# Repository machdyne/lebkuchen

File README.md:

# Lebkuchen Computer

Lebkuchen is an FPGA computer based on the GateMate A1.

This repo contains schematics, PCB layouts, pinouts, a 3D-printable case, example gateware and documentation.

Find more information on the [Lebkuchen product page](https://machdyne.com/product/lebkuchen-computer/).

## Programming Lebkuchen 

Lebkuchen can be programmed over USB-C or by copying gateware to a MicroSD card (not yet implemented). The FPGA is configured by the onboard RP2040, which can load the configuration from onboard flash, a FAT-formatted MicroSD card or over the USB-JTAG bridge.

### JTAG

Program the FPGA configuration SRAM:

```
openFPGALoader -c dirtyJtag image.bit
```

### 3.5mm TRRS Audio Jack

| Pin | Signal |
| --- | ------ |
| T | Left Audio |
| R1 | Right Audio |
| R2 | Composite Video |
| S | GND |

## Resources

 * [fpga-dac audio player](https://github.com/machdyne/fpga-dac)

## License

The contents of this repo are released under the [Lone Dynamics Open License](LICENSE.md).

Note: You can use these designs for commercial purposes but we ask that instead of producing exact clones, that you either replace our trademarks and logos with your own or add your own next to ours.

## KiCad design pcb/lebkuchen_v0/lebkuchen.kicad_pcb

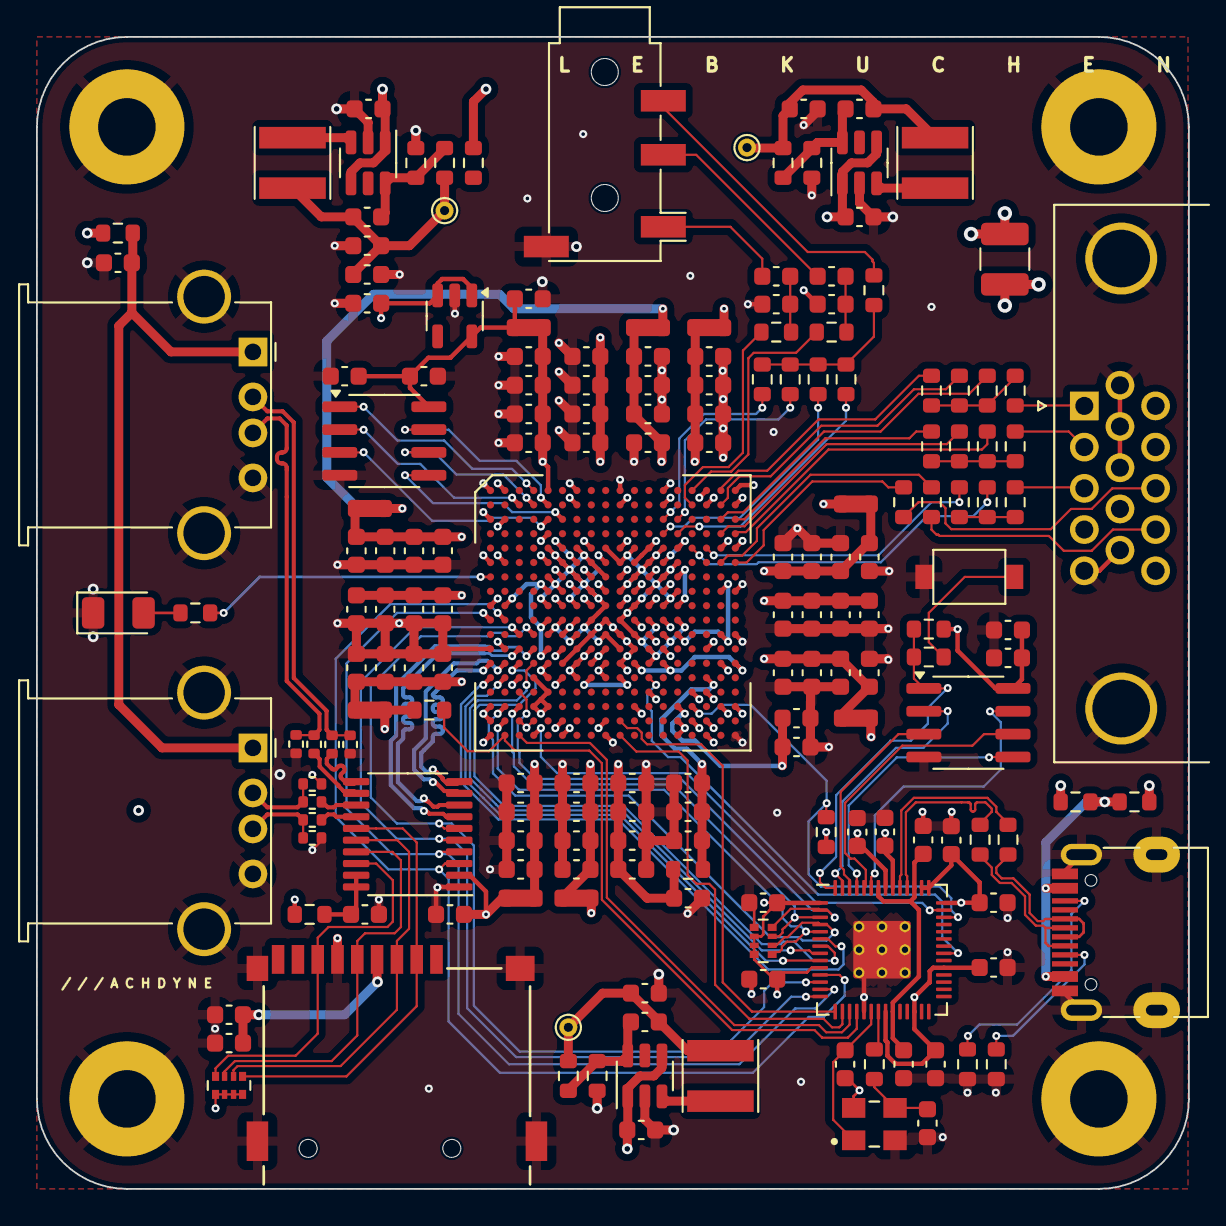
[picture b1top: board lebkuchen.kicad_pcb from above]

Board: 4 copper layers, 64.0 x 64.0 mm, 185 parts (0 on the bottom side), 116 nets.

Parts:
C1, C2, C3, C12, C16, C18, C19, C27, C28, C36, C37, C45, C46, C55, C56: 2.2uF; C_0603_1608Metric
C4, C5, C6, C21, C22, C29, C30, C38, C39, C47, C48, C57, C58: 470nF; C_0603_1608Metric
C7: 220nF; C_0603_1608Metric
C8, C9, C10, C11, C17, C20, C23, C24, C31, C32, C40, C41, C49, C50, C59, C60, C64, C65, C67, C68, C69, C71, C83, C84, C85, C86, C87, C88, C90, C91, C95: 100nF; C_0603_1608Metric
C13, C14, C15, C25, C26, C33, C34, C42, C43, C51, C52, C61, C62: 10nF; C_0603_1608Metric
C35, C66, C89, C96, C97: 1uF; C_0603_1608Metric
C44, C80, C81: 22uF; C_0603_1608Metric
C53, C78, C79, C92, C93, C94: 10uF; C_0603_1608Metric
C54, C63: 15pF; C_0603_1608Metric
C72, C73, C74: 4.7uF; C_0603_1608Metric
C75, C76, C77: 10pF; C_0603_1608Metric
D2: LED; LED_1206_3216Metric
F1: Polyfuse; Fuse_1210_3225Metric
FB1, FB2, FB3, FB4: Ferrite_Bead; R_0603_1608Metric
H1, H2, H3, H4: MountingHole_Pad; MountingHole_3.2mm_M3_Pad
J1: TYPE-C-31-M-12-FIXED; USB_C_Receptacle_HRO_TYPE-C-31-M-12-BIG-PADS-PASTE
J3: AudioJack4; Jack_3.5mm_PJ320D_Horizontal
J4: MICROSD; SDCARD
J5, J6: USB_A; USB_A_Stewart_SS-52100-001_Horizontal
L1, L2, L3: 2.2uH; L_Taiyo-Yuden_MD-4040
R1: 4K7; R_0603_1608Metric
R2, R20: 5K1; R_0603_1608Metric
R6, R38: 10K; R_0603_1608Metric
R9, R11, R12, R13, R14, R16, R17, R18, R19: 0R; LD-NETTIE-0603
R10, R15: 27R; R_0603_1608Metric
R23, R24: 200K; R_0603_1608Metric
R25: 44K2; R_0603_1608Metric
R26, R29: 150K; R_0603_1608Metric
R27: 47K; R_0603_1608Metric
R28: 100K; R_0603_1608Metric
R30: 22R; R_0603_1608Metric
R31, R32, R33, R34: 22R; R_0402_1005Metric
R37, R39, R44, R51, R54, R58: 1K; R_0603_1608Metric
R40, R41, R67, R68: 100R; R_0603_1608Metric
R42, R52, R56, R60: 270R; R_0603_1608Metric
R43, R53, R57, R61: 536R; R_0603_1608Metric
R45: 2K; R_0603_1608Metric
R47, R64, R65, R66: 51R; R_0603_1608Metric
R55, R59, R62, R63: 15K; R_0402_1005Metric
RN1: 20K; R_Array_Convex_4x0402
RN2: 4K7; R_Array_Convex_4x0402
SW1: BOOT; Button_2P_3x4mm
TP1: TP_PWR3V3; TestPoint_THTPad_D1.0mm_Drill0.5mm
TP2: TP_PWR2V5; TestPoint_THTPad_D1.0mm_Drill0.5mm
TP3: TP_PWR1V0; TestPoint_THTPad_D1.0mm_Drill0.5mm
U1: CCGM1A1; BGA-324_15.0x15.0mm_Layout18x18_P0.8mm_Ball0.5mm_Pad0.4mm_N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
U2: RP2040; RP2040-QFN-56-OFFICIAL
U3: APS6404L-SQN-SN; SOIC-8_3.9x4.9mm_P1.27mm
U4: LSF0108PWR; TSSOP-20_4.4x6.5mm_P0.65mm
U5: AT25FF321A-SSHN-B; SOIC-8_3.9x4.9mm_P1.27mm
U7: NCP164ASN180T1G; TSOT-23-5
U8, U9, U10: TLV62569DDC; SOT-23-6
VGA1: DB15_Female_MountingHoles; DSUB-15-HD_Female_Horizontal_P2.29x1.98mm_EdgePinOffset3.03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
Y2: ECS-80-12-33-JGN-TR-12MHZ; XTAL_ECS-240-8-33-AGN-TR

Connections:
/AUDIO_L: R40.1, U1.B15 (IO_EB_A8)
/AUDIO_LC: C92.1, J3.T
/AUDIO_R: R41.1, U1.A15 (IO_EB_B8)
/AUDIO_RC: C93.1, J3.R1
/BOOT: R39.1, SW1.1
/CDONE: U1.V3 (IO_WA_B2/CFG_DONE), U2.17 (GPIO14)
/CFAILED: R1.2, U1.V2 (IO_WA_A2/~CFG_FAILED), U2.18 (GPIO15)
/CFG_MD3: U1.V4 (CFG_MD3/IO_WA_B1), U2.41 (GPIO29/ADC3)
/CLKRP: U1.P12 (CLK1/IO_SB_A7), U2.35 (GPIO23)
/CSPI_MISO: U1.P1 (IO_WA_A7/SPI_D1), U2.6 (GPIO4)
/CSPI_MOSI: U1.P2 (IO_WA_B7/SPI_D0), U2.9 (GPIO7)
/CSPI_SCK: U1.N4 (IO_WA_B8/SPI_CLK), U2.8 (GPIO6)
/CSPI_SS: U1.N3 (IO_WA_A8/~SPI_CS), U2.7 (GPIO5)
/JTAG_TCK: RN2.4 (R4.1), U1.R3 (JTAG_TCK/IO_WA_A5), U2.2 (GPIO0)
/JTAG_TDI: RN2.2 (R2.1), U1.T2 (JTAG_TDI/IO_WA_A4), U2.4 (GPIO2)
/JTAG_TDO: RN2.1 (R1.1), U1.U2 (JTAG_TDO/IO_WA_B3), U2.5 (GPIO3)
/JTAG_TMS: RN2.3 (R3.1), U1.T3 (JTAG_TMS/IO_WA_B4), U2.3 (GPIO1)
/LED: R51.1, U1.G1 (IO_WC_A0)
/PWR1V0: C1.2, C2.2, C4.2, C5.2, C9.2, C10.2, C13.2, C14.2, C18.2, C19.2, C20.2, C21.2, C22.2, C23.2, C24.2, C25.2, C26.2, C77.1, C80.1, C81.1, L3.2, R28.1, R30.2, TP3.1, U1.F9 (VDD), U1.G6 (VDD), U1.G8 (VDD), U1.G10 (VDD), U1.G12 (VDD), U1.H7 (VDD), U1.H9 (VDD), U1.H11 (VDD), U1.H13 (VDD), U1.J6 (VDD), U1.J8 (VDD), U1.J10 (VDD), U1.J12 (VDD), U1.K7 (VDD), U1.K9 (VDD), U1.K11 (VDD), U1.K13 (VDD), U1.L6 (VDD), U1.L8 (VDD), U1.L10 (VDD), U1.L12 (VDD), U1.M7 (VDD), U1.M9 (VDD), U1.M11 (VDD), U1.M13 (VDD), U1.N6 (VDD), U1.N8 (VDD), U1.N10 (VDD)
/PWR1V0RP: C64.1, C68.1, U2.23 (DVDD), U2.45 (VREG_VOUT), U2.50 (DVDD)
/PWR1V8: C17.1, C35.1, C97.1, R11.2, U3.8 (VCC), U7.5 (OUT)
/PWR2V5: C8.2, C16.2, C66.1, C69.1, C71.1, C76.1, C79.1, C83.1, C84.1, C85.1, C86.1, C87.1, C88.1, C89.1, L2.2, R1.1, R6.1, R9.2, R12.2, R13.2, R14.2, R16.2, R17.2, R18.2, R19.2, R26.1, R38.1, RN2.6 (R3.2), RN2.7 (R2.2), RN2.8 (R1.2), TP2.1, U1.T14 (VDD_CLK), U2.1 (IOVDD), U2.10 (IOVDD), U2.22 (IOVDD), U2.26 (RUN), U2.33 (IOVDD), U2.42 (IOVDD), U2.43 (ADC_AVDD), U2.44 (VREG_VIN), U2.49 (IOVDD), U4.2 (VREF_A), U5.8 (VCC)
/PWR3V3: C65.1, C75.1, C78.1, C94.1, C95.1, C96.1, J4.4 (VDD), L1.2, R23.1, R24.1, RN1.5 (R4.2), RN1.6 (R3.2), RN1.7 (R2.2), RN1.8 (R1.2), TP1.1, U2.48 (USB_VDD), U7.1 (IN), U7.3 (EN)
/PWR5V0: C72.1, C73.1, C74.1, F1.2, FB3.1, FB4.1, U8.1 (EN), U8.4 (VIN), U9.1 (EN), U9.4 (VIN), U10.1 (EN), U10.4 (VIN)
/PWR5V0R: F1.1, FB1.1, FB2.1
/RAM_IO2: U1.C5 (IO_NA_B2), U3.3 (SIO2)
/RAM_IO3: U1.B5 (IO_NA_A2), U3.7 (SIO3)
/RAM_MISO: U1.B3 (IO_NA_B0), U3.2 (SO/SIO)
/RAM_MOSI: U1.C6 (IO_NA_A3), U3.5 (SI/SIO)
/RAM_SCK: U1.B4 (IO_NA_B1), U3.6 (SCLK)
/RAM_SS: U1.A4 (IO_NA_A1), U3.1 (~CE)
/RESETN: R6.2, U1.T15 (~RESET), U2.40 (GPIO28/ADC2)
/RP_QSPI_IO0: U2.53 (QSPI_SD0), U5.5 (DI(IO0))
/RP_QSPI_IO1: U2.55 (QSPI_SD1), U5.2 (DO(IO1))
/RP_QSPI_IO2: U2.54 (QSPI_SD2), U5.3 (IO2)
/RP_QSPI_IO3: U2.51 (QSPI_SD3), U5.7 (IO3)
/RP_QSPI_SCK: U2.52 (QSPI_SCLK), U5.6 (CLK)
/RP_QSPI_SS: R38.2, R39.2, U2.56 (QSPI_CSN), U5.1 (~CS)
/SDC_MISO: J4.7 (DAT0), RN1.4 (R4.1), U4.18 (B1)
/SDC_MOSI: J4.3 (CMD), RN1.2 (R2.1), U4.16 (B3)
/SDC_SCK: J4.5 (CLK), RN1.3 (R3.1), U4.17 (B2)
/SDC_SS: J4.2 (DAT3/CD), RN1.1 (R1.1), U4.15 (B4)
/SD_MISO: U1.K2 (IO_WB_B5), U2.11 (GPIO8), U4.3 (A1)
/SD_MOSI: U1.L3 (IO_WB_A2), U2.14 (GPIO11), U4.5 (A3)
/SD_SCK: U1.K1 (IO_WB_A5), U2.13 (GPIO10), U4.4 (A2)
/SD_SS: U1.L4 (IO_WB_B2), U2.12 (GPIO9), U4.6 (A4)
/UART_RX: U1.V10 (IO_SA_B8), U2.16 (GPIO13)
/UART_TX: U1.U10 (IO_SA_A8), U2.15 (GPIO12)
/USB1C_DN: R32.2, U4.13 (B6)
/USB1C_DP: R31.2, U4.14 (B5)
/USB1_CONN_DN: J6.2 (D-), R32.1, R59.1
/USB1_CONN_DP: J6.3 (D+), R31.1, R55.1
/USB1_DN: U1.M3 (IO_WB_A1), U4.8 (A6)
/USB1_DP: U1.M4 (IO_WB_B1), U4.7 (A5)
/USB2C_DN: R34.2, U4.11 (B8)
/USB2C_DP: R33.2, U4.12 (B7)
/USB2_CONN_DN: J5.2 (D-), R34.1, R63.1
/USB2_CONN_DP: J5.3 (D+), R33.1, R62.1
/USB2_DN: U1.N1 (IO_WB_A0), U4.10 (A8)
/USB2_DP: U1.N2 (IO_WB_B0), U4.9 (A7)
/USB_CONN_DN: J1.A7 (DN1), J1.B7 (DN2), R10.1
/USB_CONN_DP: J1.A6 (DP1), J1.B6 (DP2), R15.1
/USB_DN: R10.2, U2.46 (USB_DM)
/USB_DP: R15.2, U2.47 (USB_DP)
/VBUS: C53.1, FB3.2, J5.1 (VBUS), J6.1 (VBUS)
/VBUSC: FB1.2, FB2.2, J1.A4 (VBUS), J1.A9 (VBUS), J1.B4 (VBUS), J1.B9 (VBUS)
/VDD_EA: C37.2, C39.2, C41.2, C43.2, R14.1, U1.G14 (VDD_EA), U1.H17 (VDD_EA), U1.J14 (VDD_EA), U1.L14 (VDD_EA), U1.L17 (VDD_EA)
/VDD_EB: C36.2, C38.2, C40.2, C42.2, R13.1, U1.A16 (VDD_EB), U1.B18 (VDD_EB), U1.E14 (VDD_EB), U1.E17 (VDD_EB), U1.F13 (VDD_EB)
/VDD_NA: C27.2, C29.2, C31.2, C33.2, R11.1, U1.A5 (VDD_NA), U1.B7 (VDD_NA), U1.E6 (VDD_NA), U1.E8 (VDD_NA), U1.F7 (VDD_NA)
/VDD_NB: C28.2, C30.2, C32.2, C34.2, R12.1, U1.B10 (VDD_NB), U1.B13 (VDD_NB), U1.E10 (VDD_NB), U1.E12 (VDD_NB), U1.F11 (VDD_NB)
/VDD_PLL: C7.2, C12.2, C44.2, R30.1, U1.P16 (VDD_PLL)
/VDD_SA: C46.2, C48.2, C50.2, C52.2, R17.1, U1.P6 (VDD_SA), U1.P8 (VDD_SA), U1.P10 (VDD_SA), U1.U6 (VDD_SA), U1.U9 (VDD_SA)
/VDD_SB: C45.2, C47.2, C49.2, C51.2, R16.1, U1.N11 (VDD_SB), U1.N13 (VDD_SB), U1.N18 (VDD_SB), U1.R15 (VDD_SB), U1.T18 (VDD_SB)
/VDD_WA: C3.2, C6.2, C11.2, C15.2, R9.1, U1.N5 (VDD_WA), U1.P3 (VDD_WA), U1.P5 (VDD_WA), U1.T1 (VDD_WA), U1.U1 (POR_EN/IO_WA_A3), U1.U3 (VDD_WA), U1.U4 (CFG_MD2/IO_WA_A1)
/VDD_WB: C56.2, C58.2, C60.2, C62.2, R19.1, U1.H5 (VDD_WB), U1.J2 (VDD_WB), U1.K5 (VDD_WB), U1.M2 (VDD_WB), U1.M5 (VDD_WB)
/VDD_WC: C55.2, C57.2, C59.2, C61.2, R18.1, U1.A2 (VDD_WC), U1.C2 (VDD_WC), U1.D5 (VDD_WC), U1.F2 (VDD_WC), U1.F5 (VDD_WC)
/VGA_B0: R60.2, U1.E16 (IO_EB_A3)
/VGA_B1: R61.2, U1.E15 (IO_EB_B3)
/VGA_BLUE: R60.1, R61.1, R66.2
/VGA_B_CONN: R66.1, VGA1.3
/VGA_G0: R56.2, U1.C18 (IO_EB_A4)
/VGA_G1: R57.2, U1.D17 (IO_EB_B2)
/VGA_G2: R58.2, U1.D18 (IO_EB_A2)
/VGA_GREEN: R56.1, R57.1, R58.1, R65.2
/VGA_G_CONN: R65.1, VGA1.2
/VGA_HS: R67.2, U1.F18 (IO_EB_A0)
/VGA_HS_CONN: R67.1, VGA1.13
/VGA_R0: R52.2, U1.A17 (IO_EB_B5)
/VGA_R1: R53.2, U1.B17 (IO_EB_A5)
/VGA_R2: R54.2, U1.C17 (IO_EB_B4)
/VGA_RED: R52.1, R53.1, R54.1, R64.2
/VGA_R_CONN: R64.1, VGA1.1
/VGA_VS: R68.2, U1.F17 (IO_EB_B0)
/VGA_VS_CONN: R68.1, VGA1.14
/VIDEO_C: J3.R2, R47.2
/VIDEO_D0: R42.1, U1.C13 (IO_NB_B6)
/VIDEO_D1: R43.1, U1.C14 (IO_NB_B8)
/VIDEO_D2: R44.1, U1.D13 (IO_NB_A6)
/VIDEO_D3: R45.1, U1.D14 (IO_NB_A8)
/XIN: C54.2, U2.20 (XIN), Y2.1 (IN/OUT)
/XOUT: R37.2, U2.21 (XOUT)
GND: C1.1, C2.1, C3.1, C4.1, C5.1, C6.1, C7.1, C8.1, C9.1, C10.1, C11.1, C12.1, C13.1, C14.1, C15.1, C16.1, C17.2, C18.1, C19.1, C20.1, C21.1, C22.1, C23.1, C24.1, C25.1, C26.1, C27.1, C28.1, C29.1, C30.1, C31.1, C32.1, C33.1, C34.1, C35.2, C36.1, C37.1, C38.1, C39.1, C40.1, C41.1, C42.1, C43.1, C44.1, C45.1, C46.1, C47.1, C48.1, C49.1, C50.1, C51.1, C52.1, C53.2, C54.1, C55.1, C56.1, C57.1, C58.1, C59.1, C60.1, C61.1, C62.1, C63.2, C64.2, C65.2, C66.2, C67.2, C68.2, C69.2, C71.2, C72.2, C73.2, C74.2, C78.2, C79.2, C80.2, C81.2, C83.2, C84.2, C85.2, C86.2, C87.2, C88.2, C89.2, C90.2, C91.2, C94.2, C95.2, C96.2, C97.2, D2.1 (K), H1.1, H2.1, H3.1, H4.1, J1.A1 (GND), J1.A12 (GND), J1.B1 (GND), J1.B12 (GND), J1.S1 (SHIELD), J1.S2 (SHIELD), J1.S3 (SHIELD), J1.S4 (SHIELD), J3.S, J4.6 (VSS), J5.4 (GND), J5.5 (Shield), J6.4 (GND), J6.5 (Shield), R2.2, R20.2, R25.2, R27.2, R29.2, R55.2, R59.2, R62.2, R63.2, RN2.5 (R4.2), SW1.2, U1.A1 (GND), U1.A7 (GND), U1.A10 (GND), U1.A13 (GND), U1.A18 (GND), U1.B16 (GND), U1.C1 (GND), U1.E5 (GND), U1.E7 (GND), U1.E9 (GND), U1.E11 (GND), U1.E13 (GND), U1.E18 (GND), U1.F1 (GND), U1.F6 (GND), U1.F8 (GND), U1.F10 (GND), U1.F12 (GND), U1.F14 (GND), U1.G5 (GND), U1.G7 (GND), U1.G9 (GND), U1.G11 (GND), U1.G13 (GND), U1.H6 (GND), U1.H8 (GND), U1.H10 (GND), U1.H12 (GND), U1.H14 (GND), U1.H18 (GND), U1.J1 (GND), U1.J5 (GND), U1.J7 (GND), U1.J9 (GND), U1.J11 (GND), U1.J13 (GND), U1.K6 (GND), U1.K8 (GND), U1.K10 (GND), U1.K12 (GND), U1.K14 (GND), U1.L5 (GND), U1.L7 (GND), U1.L9 (GND), U1.L11 (GND), U1.L13 (GND), U1.L18 (GND), U1.M1 (GND), U1.M6 (GND), U1.M8 (GND), U1.M10 (GND), U1.M12 (GND), U1.M16 (GND), U1.N7 (GND), U1.N9 (GND), U1.N12 (GND), U1.N17 (GND), U1.P4 (GND), U1.P7 (GND), U1.P9 (GND), U1.R5 (CFG_MD0/IO_WA_A0), U1.R12 (GND), U1.R16 (GND), U1.T4 (GND), U1.T5 (CFG_MD1/IO_WA_B0), U1.T11 (GND), U1.T17 (GND), U1.U14 (GND), U1.U15 (GND), U1.U16 (GND), U1.V1 (GND), U1.V6 (GND), U1.V9 (GND), U1.V14 (GND), U1.V16 (GND), U1.V18 (GND), U2.19 (TESTEN), U2.57 (GND), U3.4 (VSS), U4.1 (GND), U5.4 (GND), U7.2 (GND), U8.2 (GND), U9.2 (GND), U10.2 (GND), VGA1.0 (PAD), VGA1.5, VGA1.6, VGA1.7, VGA1.8, VGA1.10, Y2.2 (GND), Y2.4 (GND)
unnamed: C90.1, C92.2, R40.2
unnamed: C91.1, C93.2, R41.2
unnamed: D2.2 (A), R51.2
unnamed: J1.A5 (CC1), R2.1
unnamed: J1.B5 (CC2), R20.1
unnamed: R42.2, R43.2, R44.2, R45.2, R47.1
unnamed: C67.1, R23.2, U4.19 (VREF_B), U4.20 (EN)
unnamed: C75.2, R24.2, R25.1, U8.6 (FB)
unnamed: L1.1, U8.3 (SW)
unnamed: C76.2, R26.2, R27.1, U9.6 (FB)
unnamed: L2.1, U9.3 (SW)
unnamed: C77.2, R28.2, R29.1, U10.6 (FB)
unnamed: L3.1, U10.3 (SW)
unnamed: C63.1, R37.1, Y2.3 (OUT/IN)

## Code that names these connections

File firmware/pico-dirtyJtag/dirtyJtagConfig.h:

#ifndef DirtyJtagConfig_h
#define DirtyJtagConfig_h

// Set to 0 to disable USB-CDC-UART bridge
#define USB_CDC_UART_BRIDGE  1


#define BOARD_PICO           0
#define BOARD_ADAFRUIT_ITSY  1
#define BOARD_SPOKE_RP2040   2
#define BOARD_QMTECH_RP2040_DAUGHTERBOARD 3
#define BOARD_WERKZEUG       4
#define BOARD_LEBKUCHEN         100

// Select the board type from the above
#define BOARD_TYPE BOARD_LEBKUCHEN
//#define BOARD_TYPE BOARD_ADAFRUIT_ITSY
//#define BOARD_TYPE BOARD_SPOKE_RP2040
//#define BOARD_TYPE BOARD_WERKZEUG
//#define BOARD_TYPE BOARD_QMTECH_RP2040_DAUGHTERBOARD

// General mapping
// TDI  SPIO RX
// TDO  SPIO TX
// TCK  SPIO SCK
// TMS  SPIO CS
// RST  GPIO
// TRST GPIO

#if ( BOARD_TYPE == BOARD_PICO )

#define PIN_TDI 16 
#define PIN_TDO 17
#define PIN_TCK 18
#define PIN_TMS 19
#define PIN_RST 20
#define PIN_TRST 21

#define LED_INVERTED   0
#define PIN_LED_TX     25
#define PIN_LED_ERROR  25
#define PIN_LED_RX     25

#if ( USB_CDC_UART_BRIDGE )
#define PIN_UART       uart0
#define PIN_UART_TX    12
#define PIN_UART_RX    13
#endif // USB_CDC_UART_BRIDGE

#elif ( BOARD_TYPE == BOARD_ADAFRUIT_ITSY )

#define PIN_TDI 28 
#define PIN_TDO 27
#define PIN_TCK 26
#define PIN_TMS 29
#define PIN_RST 24
#define PIN_TRST 25

// no regular LEDs on the Itsy - it's a neopixel
#define LED_INVERTED   0
#define PIN_LED_TX     -1
#define PIN_LED_ERROR  -1
#define PIN_LED_RX     -1

#if ( USB_CDC_UART_BRIDGE )
#define PIN_UART       uart0
#define PIN_UART_TX    0
#define PIN_UART_RX    1
#endif // USB_CDC_UART_BRIDGE

#elif ( BOARD_TYPE == BOARD_SPOKE_RP2040 )

#define PIN_TDI 23 
#define PIN_TDO 20
#define PIN_TCK 22
#define PIN_TMS 21
#define PIN_RST 26
#define PIN_TRST 27

#define LED_INVERTED   1
#define PIN_LED_TX     16
#define PIN_LED_ERROR  17
#define PIN_LED_RX     18

#if ( USB_CDC_UART_BRIDGE )
#define PIN_UART       uart0
#define PIN_UART_TX    28
#define PIN_UART_RX    29
#endif // USB_CDC_UART_BRIDGE


#elif ( BOARD_TYPE == BOARD_WERKZEUG )

#define PIN_TDI 1
#define PIN_TDO 2
#define PIN_TCK 0
#define PIN_TMS 3
#define PIN_RST 4
#define PIN_TRST 5

#define LED_INVERTED   1
#define PIN_LED_TX     20
#define PIN_LED_ERROR  21
#define PIN_LED_RX     20

#if ( USB_CDC_UART_BRIDGE )
#define PIN_UART       uart0
#define PIN_UART_TX    28
#define PIN_UART_RX    29
#endif // USB_CDC_UART_BRIDGE

#elif ( BOARD_TYPE == BOARD_LEBKUCHEN )

#define PIN_TCK 0
#define PIN_TDI 2
#define PIN_TDO 3
#define PIN_TMS 1

#define PIN_RST 8
#define PIN_TRST 9

#define PIN_CDONE		14
#define PIN_CFAILED	15
#define PIN_CRESET	28
#define PIN_CLK		23
#define PIN_CFG_MD3  29

#define LED_INVERTED   0
#define PIN_LED_TX     -1
#define PIN_LED_ERROR  -1
#define PIN_LED_RX     -1

#if ( USB_CDC_UART_BRIDGE )
#define PIN_UART       uart0
#define PIN_UART_TX    12
#define PIN_UART_RX    13
#endif // USB_CDC_UART_BRIDGE


#elif ( BOARD_TYPE == BOARD_QMTECH_RP2040_DAUGHTERBOARD )

// in rp2040 daughterboard UART pins are connected to FPGA pins
// depending on the FPGA pin configuration there is a possibility
// of damage so these pins are not going to be setup
#define USB_CDC_UART_BRIDGE  0

#define PIN_TDI  16 
#define PIN_TDO  17
#define PIN_TCK  18
#define PIN_TMS  19
// in rp2040 daughterboard these pins are connected to FPGA pins
// depending on the FPGA pin configuration there is a possibility
// of damage so these pins are not going to be setup
// #define PIN_RST  X
// #define PIN_TRST X

#define LED_INVERTED   0
#define PIN_LED_TX     25
#define PIN_LED_ERROR  25
#define PIN_LED_RX     25

#endif // BOARD_TYPE

#endif // DirtyJtagConfig_h

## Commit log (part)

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2025-07-15 add render
